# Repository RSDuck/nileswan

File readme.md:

# nileswan

An attempt at creating flash cartridge for Wonderswan.

Expect exciting things here.

## Building instructions

### Requirements

- [OSS CAD Suite](https://github.com/YosysHQ/oss-cad-suite-build) (FPGA core)
  - Requires a modified version of `icepack`, see below for more information
- [Wonderful Toolchain](https://wonderful.asie.pl/wiki/doku.php?id=getting_started) (IPL1, recovery, updater)
- CMake (MCU firmware)
- NASM (IPL0)
- Nim 2.0+ (FPGA core, IPL0)
- Ninja (MCU firmware)
- Python 3.x (SPI images, updater)
  - + `crc` library
- dd, dosfstools, mtools (emulator images)

#### icepack

For the FPGA to be ready in time, the bitstream needs to be loaded at the highest speed possible. I created a [PR](https://github.com/YosysHQ/icestorm/pull/332) for icepack which adds a setting to change this. Without it is not possible to compile the FPGA bitstream.

### Compiling

1. Make sure to fetch the Git submodules: `git submodule update --init --recursive`.
2. Run `make help` to read what build options are possible.
3. Run `make` (or `make ...`) to build the requested components.

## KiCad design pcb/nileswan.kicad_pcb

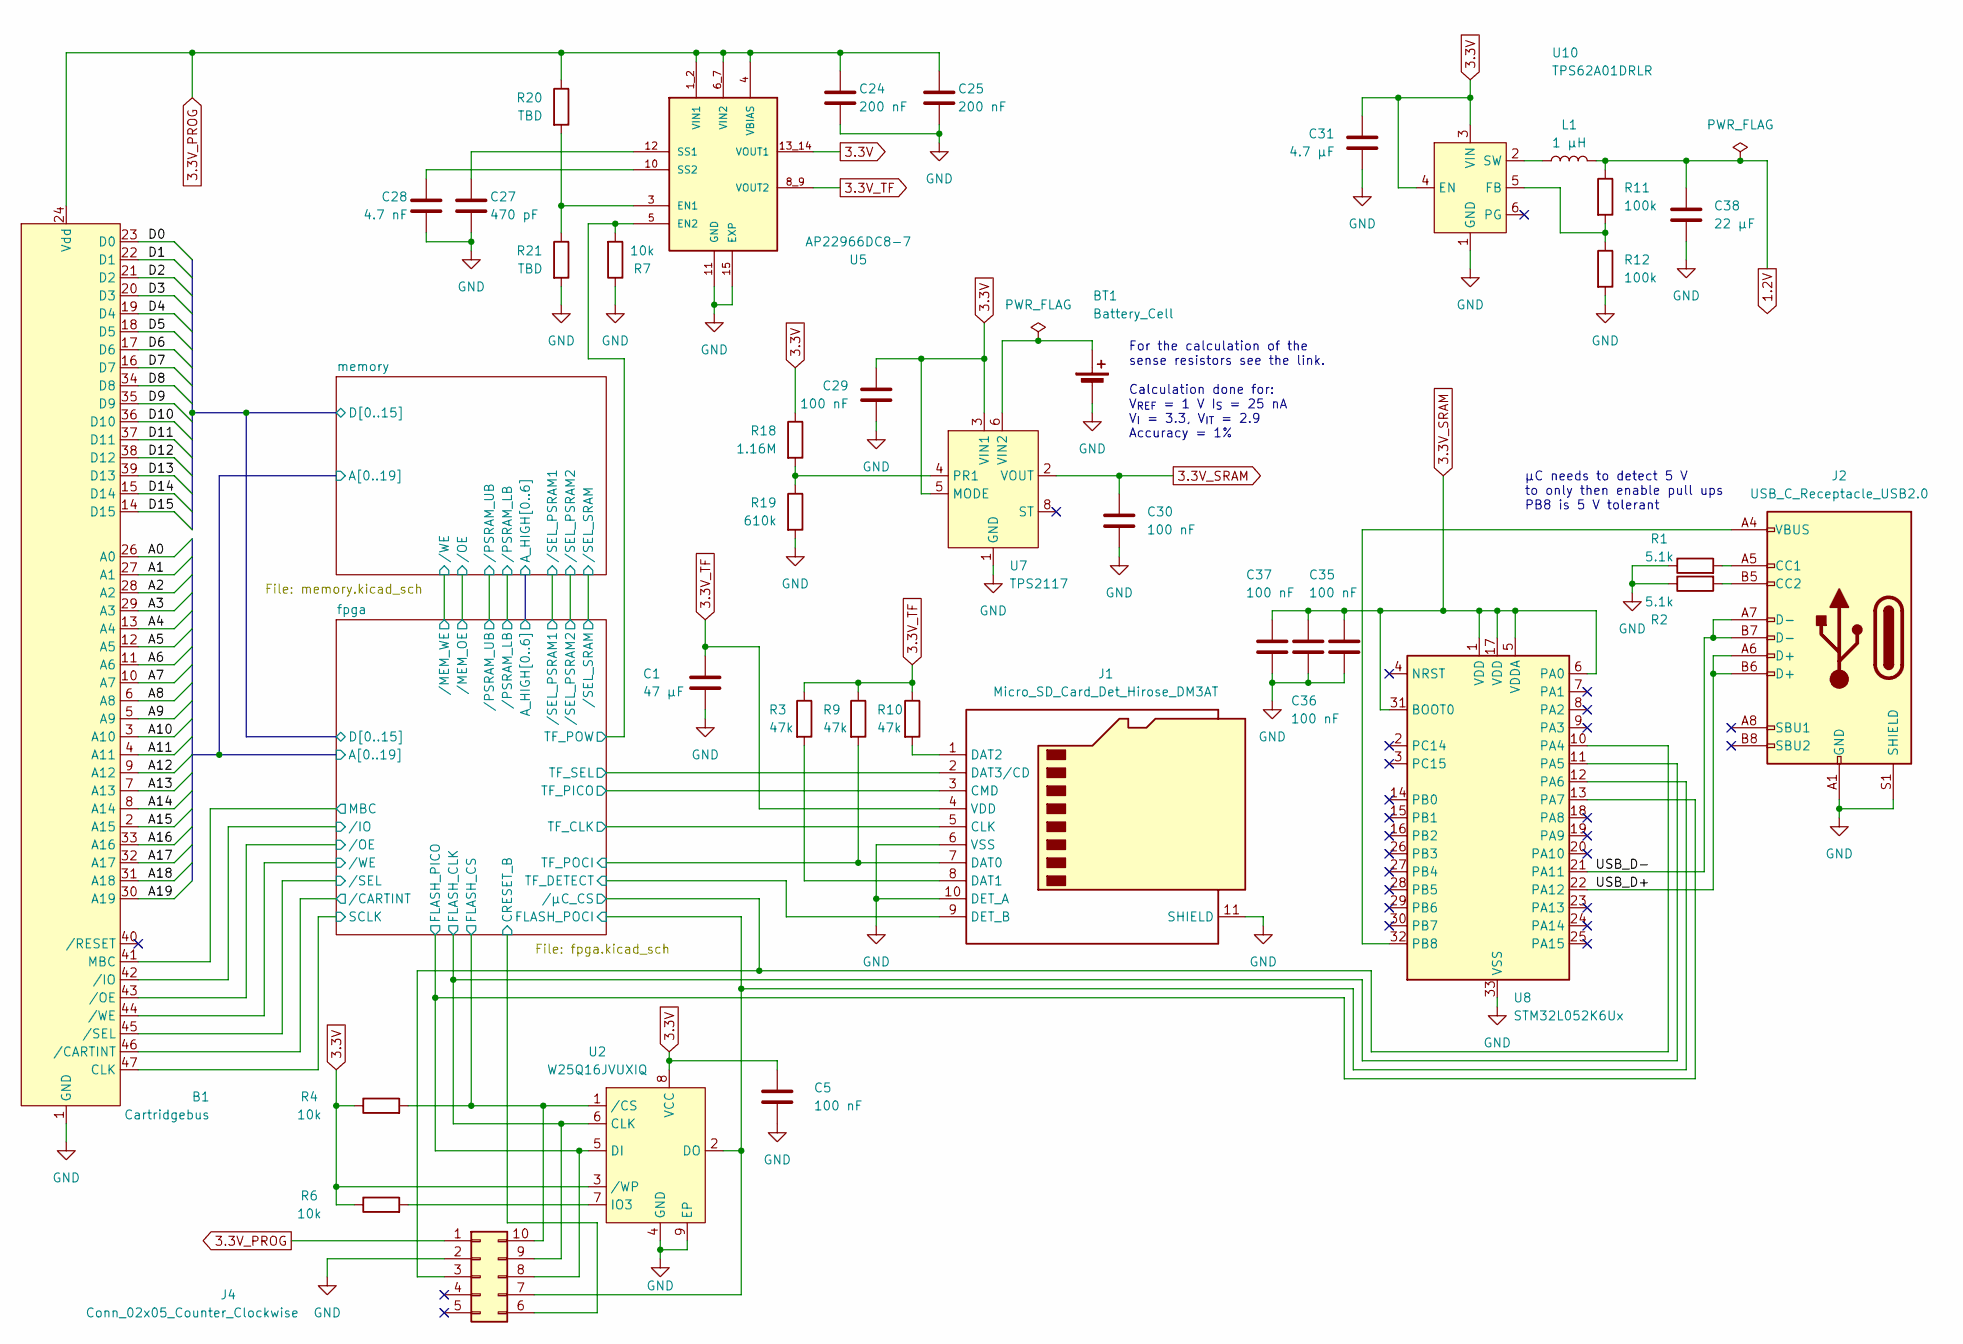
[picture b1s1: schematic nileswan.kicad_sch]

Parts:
B1: Cartridgebus; WSCartridgeBus
BT1: Battery_Cell; BAT_BAT-HLD-012-SMT
C1: 47 μF; C_0805_2012Metric
C5, C29, C30, C35, C36, C37: 100 nF; C_0402_1005Metric
C24, C25: 200 nF; C_0402_1005Metric
C27: 470 pF; C_0402_1005Metric
C28: 4.7 nF; C_0402_1005Metric
C31: 4.7 μF; C_0603_1608Metric
C38: 22 μF; C_0603_1608Metric
J1: Micro_SD_Card_Det_Hirose_DM3AT; microSD_HC_Hirose_DM3AT-SF-PEJM5
J2: USB_C_Receptacle_USB2.0; USB_C_Receptacle_GCT_USB4110
J4: Conn_02x05_Counter_Clockwise; Tag-Connect_TC2050-IDC-NL_2x05_P1.27mm_Vertical
L1: 1 μH; L_Murata_DFE201610P
R1, R2: 5.1k; R_0402_1005Metric
R3, R9, R10: 47k; R_0402_1005Metric
R4, R6, R7: 10k; R_0402_1005Metric
R11: 100k; R_0402_1005Metric
R12: 100k; C_0402_1005Metric
R18: 1.16M; R_0402_1005Metric
R19: 610k; R_0402_1005Metric
R20, R21: TBD; R_0402_1005Metric
U2: W25Q16JVUXIQ; SON50P300X200X60-9N
U5: AP22966DC8-7; IC_AP22966DC8-7; PARTREV 3-2
U7: TPS2117; SOTFL50P160X60-8N
U8: STM32L052K6Ux; QFN-32-1EP_5x5mm_P0.5mm_EP3.45x3.45mm
U10: TPS62A01DRLR; SOT-563

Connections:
1.2V: C38.1, L1.2, R11.1; also elsewhere on the board
3.3V: C5.1, C29.1, C31.1, R4.1, R6.1, R18.1, U2.3 (/WP), U2.8 (VCC), U5.13_14 (VOUT1), U7.3 (VIN1), U7.5 (MODE), U10.3 (VIN), U10.4 (EN); also elsewhere on the board
3.3V_PROG: B1.24 (Vdd), B1.25 (Vdd), C24.1, C25.1, J4.1, R20.1, U5.1_2 (VIN1), U5.4 (VBIAS), U5.6_7 (VIN2)
3.3V_SRAM: C30.1, C35.1, C36.1, C37.1, U7.2 (VOUT), U7.7 (VOUT), U8.1 (VDD), U8.5 (VDDA), U8.6 (PA0), U8.17 (VDD), U8.31 (BOOT0); also elsewhere on the board
3.3V_TF: C1.1, J1.4 (VDD), R3.1, R9.1, R10.1, U5.8_9 (VOUT2)
/USB_D+: J2.A6 (D+), J2.B6 (D+), U8.22 (PA12)
/USB_D-: J2.A7 (D-), J2.B7 (D-), U8.21 (PA11)
/fpga/A0: B1.26 (A0); also elsewhere on the board
/fpga/A1: B1.27 (A1); also elsewhere on the board
/fpga/A2: B1.28 (A2); also elsewhere on the board
/fpga/A3: B1.29 (A3); also elsewhere on the board
/fpga/A4: B1.13 (A4); also elsewhere on the board
/fpga/A5: B1.12 (A5); also elsewhere on the board
/fpga/A6: B1.11 (A6); also elsewhere on the board
/fpga/A7: B1.10 (A7); also elsewhere on the board
/fpga/A8: B1.6 (A8); also elsewhere on the board
/fpga/A9: B1.5 (A9); also elsewhere on the board
/fpga/A10: B1.3 (A10); also elsewhere on the board
/fpga/A11: B1.4 (A11); also elsewhere on the board
/fpga/A12: B1.9 (A12); also elsewhere on the board
/fpga/A13: B1.7 (A13); also elsewhere on the board
/fpga/A14: B1.8 (A14); also elsewhere on the board
/fpga/A15: B1.2 (A15); also elsewhere on the board
/fpga/A16: B1.33 (A16); also elsewhere on the board
/fpga/A17: B1.32 (A17); also elsewhere on the board
/fpga/A18: B1.31 (A18); also elsewhere on the board
/fpga/A19: B1.30 (A19); also elsewhere on the board
/fpga/CRESET_B: J4.6; also elsewhere on the board
/fpga/D0: B1.23 (D0); also elsewhere on the board
/fpga/D1: B1.22 (D1); also elsewhere on the board
/fpga/D2: B1.21 (D2); also elsewhere on the board
/fpga/D3: B1.20 (D3); also elsewhere on the board
/fpga/D4: B1.19 (D4); also elsewhere on the board
/fpga/D5: B1.18 (D5); also elsewhere on the board
/fpga/D6: B1.17 (D6); also elsewhere on the board
/fpga/D7: B1.16 (D7); also elsewhere on the board
/fpga/D8: B1.34 (D8); also elsewhere on the board
/fpga/D9: B1.35 (D9); also elsewhere on the board
/fpga/D10: B1.36 (D10); also elsewhere on the board
/fpga/D11: B1.37 (D11); also elsewhere on the board
/fpga/D12: B1.38 (D12); also elsewhere on the board
/fpga/D13: B1.39 (D13); also elsewhere on the board
/fpga/D14: B1.15 (D14); also elsewhere on the board
/fpga/D15: B1.14 (D15); also elsewhere on the board
/fpga/FLASH_CLK: J4.9, U2.6 (CLK), U8.11 (PA5); also elsewhere on the board
/fpga/FLASH_CS: J4.10, R4.2, U2.1 (/CS); also elsewhere on the board
/fpga/FLASH_PICO: J4.8, U2.5 (DI), U8.13 (PA7); also elsewhere on the board
/fpga/FLASH_POCI: J4.7, U2.2 (DO), U8.12 (PA6); also elsewhere on the board
/fpga/MBC: B1.41 (MBC); also elsewhere on the board
/fpga/SCLK: B1.47 (CLK); also elsewhere on the board
/fpga/TF_CLK: J1.5 (CLK); also elsewhere on the board
/fpga/TF_DETECT: J1.9 (DET_B); also elsewhere on the board
/fpga/TF_PICO: J1.3 (CMD); also elsewhere on the board
/fpga/TF_POCI: J1.7 (DAT0), R9.2; also elsewhere on the board
/fpga/TF_POW: R7.2, U5.5 (EN2); also elsewhere on the board
/fpga/TF_SEL: J1.2 (DAT3/CD); also elsewhere on the board
/fpga//CARTINT: B1.46 (/CARTINT); also elsewhere on the board
/fpga//IO: B1.42 (/IO); also elsewhere on the board
/fpga//OE: B1.43 (/OE); also elsewhere on the board
/fpga//SEL: B1.45 (/SEL); also elsewhere on the board
/fpga//WE: B1.44 (/WE); also elsewhere on the board
/fpga//μC_CS: J4.3, U8.10 (PA4); also elsewhere on the board
GND: B1.1 (GND), B1.48 (GND), BT1.2 (-), C1.2, C5.2, C24.2, C25.2, C27.2, C28.2, C29.2, C30.2, C31.2, C35.2, C36.2, C37.2, C38.2, J1.6 (VSS), J1.10 (DET_A), J1.11 (SHIELD), J2.A1 (GND), J2.A12 (GND), J2.B1 (GND), J2.B12 (GND), J2.S1 (SHIELD), J4.2, R1.1, R2.1, R7.1, R12.2, R19.2, R21.2, U2.4 (GND), U2.9 (EP), U5.11 (GND), U5.15 (EXP), U7.1 (GND), U8.33 (VSS), U10.1 (GND); also elsewhere on the board
unnamed: BT1.1 (+), U7.6 (VIN2)
unnamed: J1.8 (DAT1), R3.2
unnamed: J1.1 (DAT2), R10.2
unnamed: J2.A5 (CC1), R1.2
unnamed: J2.B5 (CC2), R2.2
unnamed: R6.2, U2.7 (IO3)
unnamed: R20.2, R21.1, U5.3 (EN1)
unnamed: C27.1, U5.12 (SS1)
unnamed: C28.1, U5.10 (SS2)
unnamed: R18.2, R19.1, U7.4 (PR1)
unnamed: J2.A4 (VBUS), J2.A9 (VBUS), J2.B4 (VBUS), J2.B9 (VBUS), U8.32 (PB8)
unnamed: R11.2, R12.1, U10.5 (FB)
unnamed: L1.1, U10.2 (SW)

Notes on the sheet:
μC needs to detect 5 V to only then enable pull ups PB8 is 5 V tolerant
For the calculation of the sense resistors see the link. Calculation done for: V_{REF} = 1 V I_{S} = 25 nA V_{I} = 3.3, V_{IT} = 2.9 Accuracy = 1%

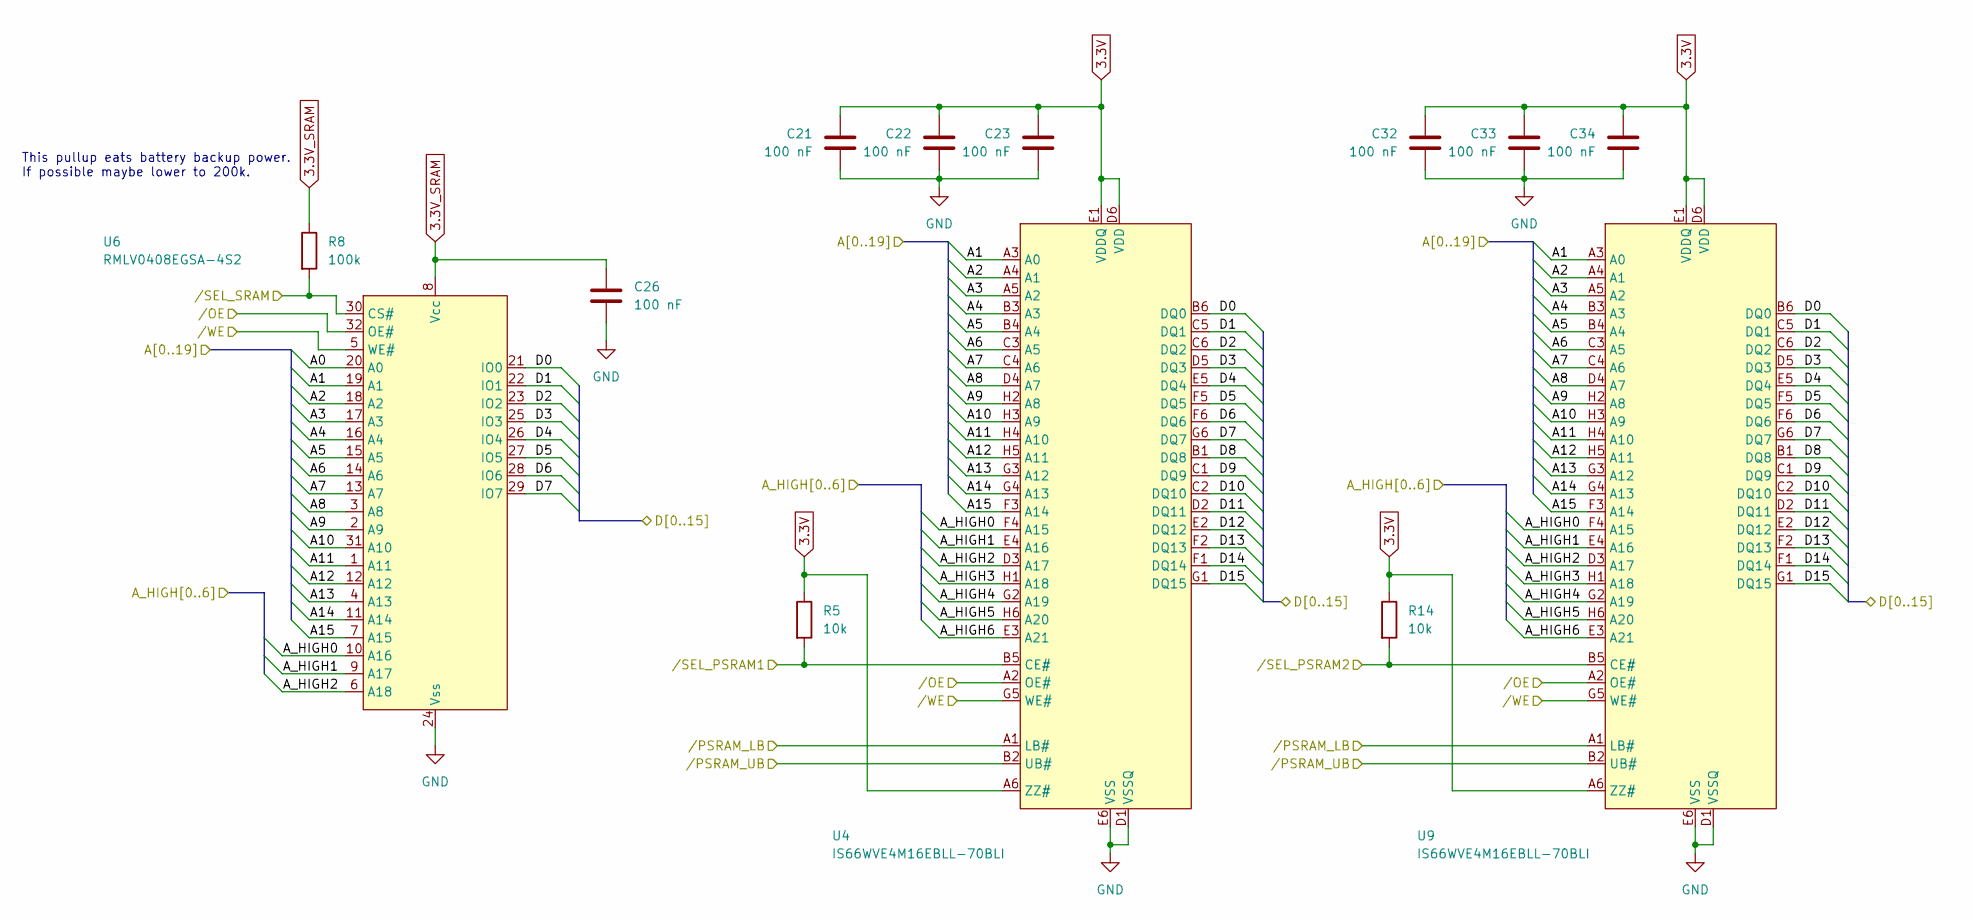
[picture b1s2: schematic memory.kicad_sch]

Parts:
C21, C22, C23, C26, C32, C33, C34: 100 nF; C_0402_1005Metric
R5, R14: 10k; R_0402_1005Metric
R8: 100k; R_0402_1005Metric
U4, U9: IS66WVE4M16EBLL-70BLI; BGA-48_6x8_6.0x8.0mm
U6: RMLV0408EGSA-4S2; sTSOP-32

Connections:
3.3V: C21.2, C22.2, C23.2, C32.2, C33.2, C34.2, R5.1, R14.1, U4.A6 (ZZ#), U4.D6 (VDD), U4.E1 (VDDQ), U9.A6 (ZZ#), U9.D6 (VDD), U9.E1 (VDDQ); also elsewhere on the board
3.3V_SRAM: C26.2, R8.1, U6.8 (Vcc); also elsewhere on the board
/fpga/A0: U6.20 (A0); also elsewhere on the board
/fpga/A1: U4.A3 (A0), U6.19 (A1), U9.A3 (A0); also elsewhere on the board
/fpga/A2: U4.A4 (A1), U6.18 (A2), U9.A4 (A1); also elsewhere on the board
/fpga/A3: U4.A5 (A2), U6.17 (A3), U9.A5 (A2); also elsewhere on the board
/fpga/A4: U4.B3 (A3), U6.16 (A4), U9.B3 (A3); also elsewhere on the board
/fpga/A5: U4.B4 (A4), U6.15 (A5), U9.B4 (A4); also elsewhere on the board
/fpga/A6: U4.C3 (A5), U6.14 (A6), U9.C3 (A5); also elsewhere on the board
/fpga/A7: U4.C4 (A6), U6.13 (A7), U9.C4 (A6); also elsewhere on the board
/fpga/A8: U4.D4 (A7), U6.3 (A8), U9.D4 (A7); also elsewhere on the board
/fpga/A9: U4.H2 (A8), U6.2 (A9), U9.H2 (A8); also elsewhere on the board
/fpga/A10: U4.H3 (A9), U6.31 (A10), U9.H3 (A9); also elsewhere on the board
/fpga/A11: U4.H4 (A10), U6.1 (A11), U9.H4 (A10); also elsewhere on the board
/fpga/A12: U4.H5 (A11), U6.12 (A12), U9.H5 (A11); also elsewhere on the board
/fpga/A13: U4.G3 (A12), U6.4 (A13), U9.G3 (A12); also elsewhere on the board
/fpga/A14: U4.G4 (A13), U6.11 (A14), U9.G4 (A13); also elsewhere on the board
/fpga/A15: U4.F3 (A14), U6.7 (A15), U9.F3 (A14); also elsewhere on the board
/fpga/A_HIGH0: U4.F4 (A15), U6.10 (A16), U9.F4 (A15); also elsewhere on the board
/fpga/A_HIGH1: U4.E4 (A16), U6.9 (A17), U9.E4 (A16); also elsewhere on the board
/fpga/A_HIGH2: U4.D3 (A17), U6.6 (A18), U9.D3 (A17); also elsewhere on the board
/fpga/A_HIGH3: U4.H1 (A18), U9.H1 (A18); also elsewhere on the board
/fpga/A_HIGH4: U4.G2 (A19), U9.G2 (A19); also elsewhere on the board
/fpga/A_HIGH5: U4.H6 (A20), U9.H6 (A20); also elsewhere on the board
/fpga/A_HIGH6: U4.E3 (A21), U9.E3 (A21); also elsewhere on the board
/fpga/D0: U4.B6 (DQ0), U6.21 (IO0), U9.B6 (DQ0); also elsewhere on the board
/fpga/D1: U4.C5 (DQ1), U6.22 (IO1), U9.C5 (DQ1); also elsewhere on the board
/fpga/D2: U4.C6 (DQ2), U6.23 (IO2), U9.C6 (DQ2); also elsewhere on the board
/fpga/D3: U4.D5 (DQ3), U6.25 (IO3), U9.D5 (DQ3); also elsewhere on the board
/fpga/D4: U4.E5 (DQ4), U6.26 (IO4), U9.E5 (DQ4); also elsewhere on the board
/fpga/D5: U4.F5 (DQ5), U6.27 (IO5), U9.F5 (DQ5); also elsewhere on the board
/fpga/D6: U4.F6 (DQ6), U6.28 (IO6), U9.F6 (DQ6); also elsewhere on the board
/fpga/D7: U4.G6 (DQ7), U6.29 (IO7), U9.G6 (DQ7); also elsewhere on the board
/fpga/D8: U4.B1 (DQ8), U9.B1 (DQ8); also elsewhere on the board
/fpga/D9: U4.C1 (DQ9), U9.C1 (DQ9); also elsewhere on the board
/fpga/D10: U4.C2 (DQ10), U9.C2 (DQ10); also elsewhere on the board
/fpga/D11: U4.D2 (DQ11), U9.D2 (DQ11); also elsewhere on the board
/fpga/D12: U4.E2 (DQ12), U9.E2 (DQ12); also elsewhere on the board
/fpga/D13: U4.F2 (DQ13), U9.F2 (DQ13); also elsewhere on the board
/fpga/D14: U4.F1 (DQ14), U9.F1 (DQ14); also elsewhere on the board
/fpga/D15: U4.G1 (DQ15), U9.G1 (DQ15); also elsewhere on the board
/fpga//MEM_OE: U4.A2 (OE#), U6.32 (OE#), U9.A2 (OE#); also elsewhere on the board
/fpga//MEM_WE: U4.G5 (WE#), U6.5 (WE#), U9.G5 (WE#); also elsewhere on the board
/fpga//PSRAM_LB: U4.A1 (LB#), U9.A1 (LB#); also elsewhere on the board
/fpga//PSRAM_UB: U4.B2 (UB#), U9.B2 (UB#); also elsewhere on the board
/fpga//SEL_PSRAM1: R5.2, U4.B5 (CE#); also elsewhere on the board
/fpga//SEL_PSRAM2: R14.2, U9.B5 (CE#); also elsewhere on the board
/fpga//SEL_SRAM: R8.2, U6.30 (CS#); also elsewhere on the board
GND: C21.1, C22.1, C23.1, C26.1, C32.1, C33.1, C34.1, U4.D1 (VSSQ), U4.E6 (VSS), U6.24 (Vss), U9.D1 (VSSQ), U9.E6 (VSS); also elsewhere on the board

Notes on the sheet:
This pullup eats battery backup power. If possible maybe lower to 200k.

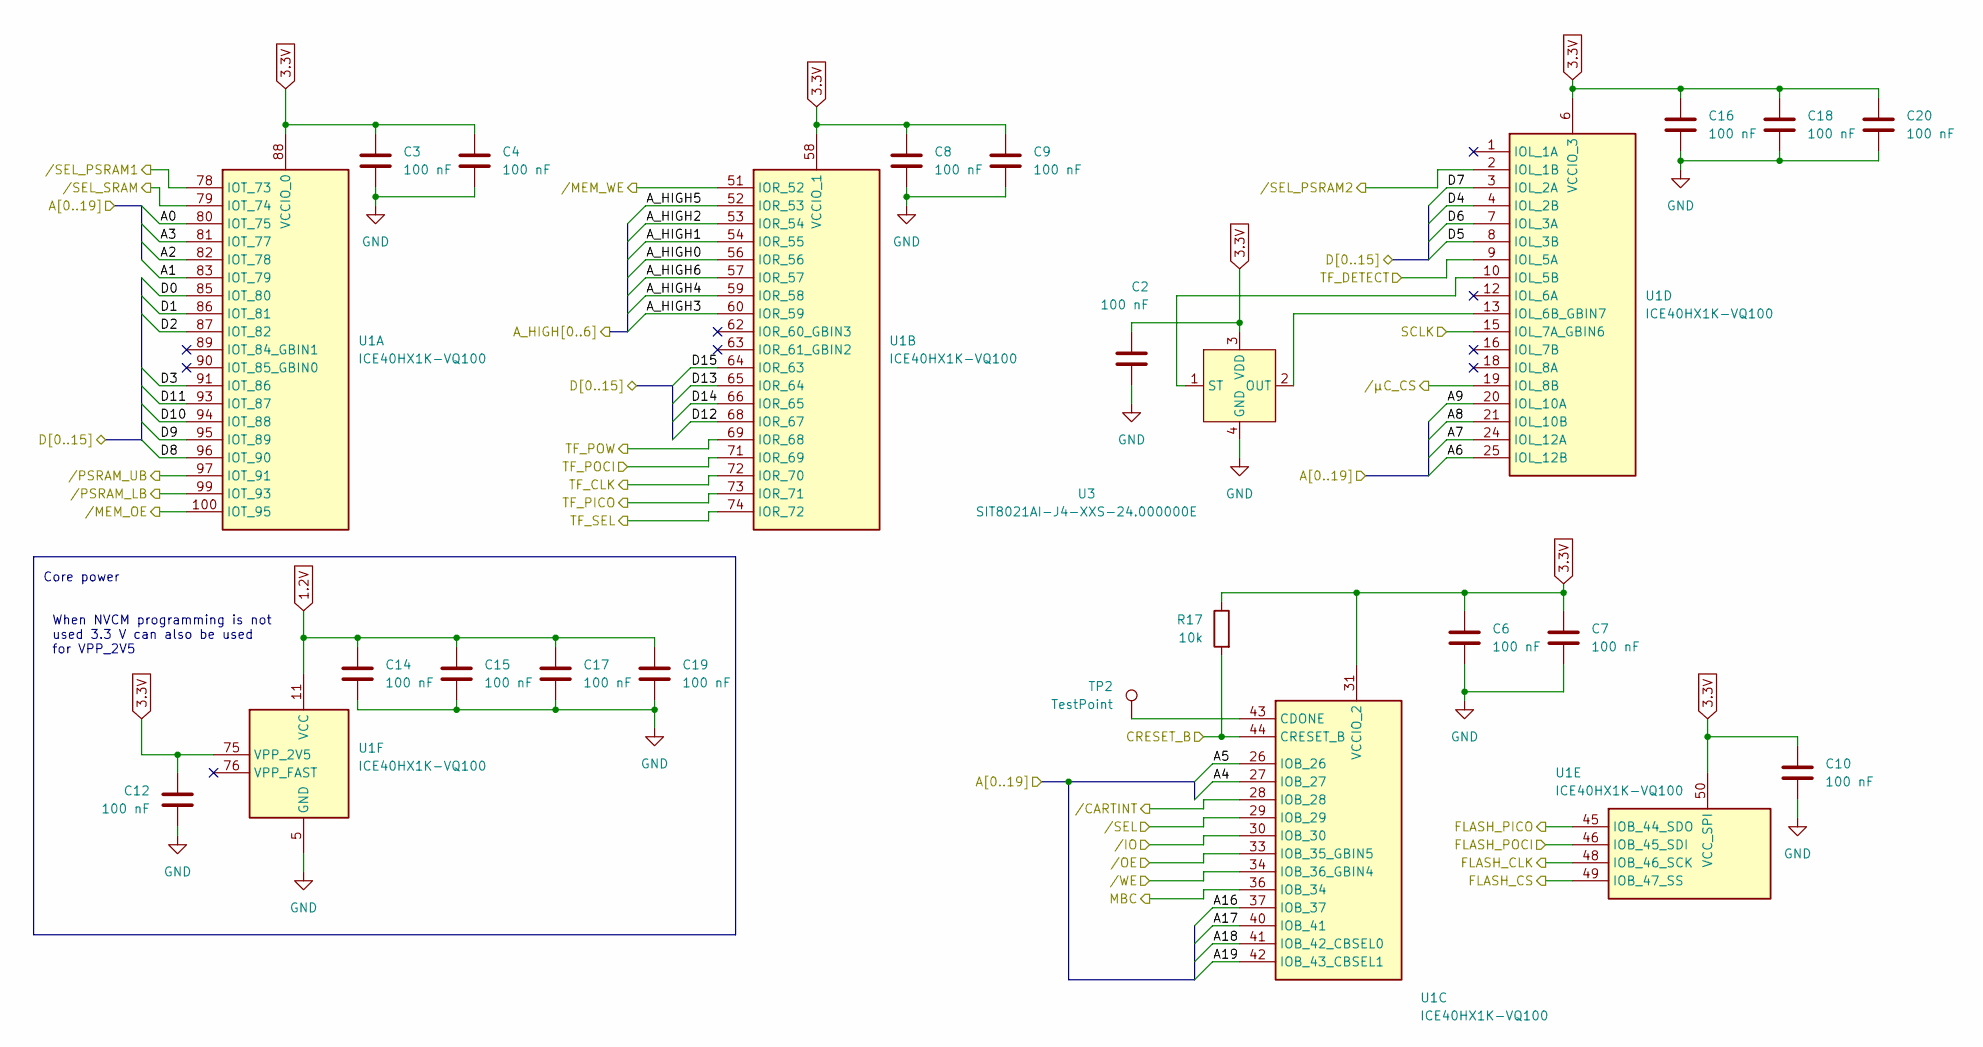
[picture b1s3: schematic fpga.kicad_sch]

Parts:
C2, C3, C4, C6, C7, C8, C9, C10, C12, C14, C15, C16, C17, C18, C19, C20: 100 nF; C_0402_1005Metric
R17: 10k; R_0402_1005Metric
TP2: TestPoint; TestPoint_Pad_D1.0mm
U1: ICE40HX1K-VQ100; VQFP-100_14x14mm_P0.5mm
U3: SIT8021AI-J4-XXS-24.000000E; BGA4N41X100P2X2_84X154X60N

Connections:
1.2V: C14.1, C15.1, C17.1, C19.1, U1.11 (VCC), U1.35 (VCC), U1.61 (VCC), U1.77 (VCC); also elsewhere on the board
3.3V: C2.1, C3.1, C4.1, C6.1, C7.1, C8.1, C9.1, C10.1, C12.1, C16.1, C18.1, C20.1, R17.1, U1.6 (VCCIO_3), U1.14 (VCCIO_3), U1.22 (VCCIO_3), U1.31 (VCCIO_2), U1.38 (VCCIO_2), U1.50 (VCC_SPI), U1.58 (VCCIO_1), U1.67 (VCCIO_1), U1.75 (VPP_2V5), U1.88 (VCCIO_0), U1.92 (VCCIO_0), U3.3 (VDD); also elsewhere on the board
/fpga/A0: U1.80 (IOT_75); also elsewhere on the board
/fpga/A1: U1.83 (IOT_79); also elsewhere on the board
/fpga/A2: U1.82 (IOT_78); also elsewhere on the board
/fpga/A3: U1.81 (IOT_77); also elsewhere on the board
/fpga/A4: U1.27 (IOB_27); also elsewhere on the board
/fpga/A5: U1.26 (IOB_26); also elsewhere on the board
/fpga/A6: U1.25 (IOL_12B); also elsewhere on the board
/fpga/A7: U1.24 (IOL_12A); also elsewhere on the board
/fpga/A8: U1.21 (IOL_10B); also elsewhere on the board
/fpga/A9: U1.20 (IOL_10A); also elsewhere on the board
/fpga/A16: U1.37 (IOB_37); also elsewhere on the board
/fpga/A17: U1.40 (IOB_41); also elsewhere on the board
/fpga/A18: U1.41 (IOB_42_CBSEL0); also elsewhere on the board
/fpga/A19: U1.42 (IOB_43_CBSEL1); also elsewhere on the board
/fpga/A_HIGH0: U1.56 (IOR_56); also elsewhere on the board
/fpga/A_HIGH1: U1.54 (IOR_55); also elsewhere on the board
/fpga/A_HIGH2: U1.53 (IOR_54); also elsewhere on the board
/fpga/A_HIGH3: U1.60 (IOR_59); also elsewhere on the board
/fpga/A_HIGH4: U1.59 (IOR_58); also elsewhere on the board
/fpga/A_HIGH5: U1.52 (IOR_53); also elsewhere on the board
/fpga/A_HIGH6: U1.57 (IOR_57); also elsewhere on the board
/fpga/CRESET_B: R17.2, U1.44 (CRESET_B); also elsewhere on the board
/fpga/D0: U1.85 (IOT_80); also elsewhere on the board
/fpga/D1: U1.86 (IOT_81); also elsewhere on the board
/fpga/D2: U1.87 (IOT_82); also elsewhere on the board
/fpga/D3: U1.91 (IOT_86); also elsewhere on the board
/fpga/D4: U1.4 (IOL_2B); also elsewhere on the board
/fpga/D5: U1.8 (IOL_3B); also elsewhere on the board
/fpga/D6: U1.7 (IOL_3A); also elsewhere on the board
/fpga/D7: U1.3 (IOL_2A); also elsewhere on the board
/fpga/D8: U1.96 (IOT_90); also elsewhere on the board
/fpga/D9: U1.95 (IOT_89); also elsewhere on the board
/fpga/D10: U1.94 (IOT_88); also elsewhere on the board
/fpga/D11: U1.93 (IOT_87); also elsewhere on the board
/fpga/D12: U1.68 (IOR_67); also elsewhere on the board
/fpga/D13: U1.65 (IOR_64); also elsewhere on the board
/fpga/D14: U1.66 (IOR_65); also elsewhere on the board
/fpga/D15: U1.64 (IOR_63); also elsewhere on the board
/fpga/FLASH_CLK: U1.48 (IOB_46_SCK); also elsewhere on the board
/fpga/FLASH_CS: U1.49 (IOB_47_SS); also elsewhere on the board
/fpga/FLASH_PICO: U1.45 (IOB_44_SDO); also elsewhere on the board
/fpga/FLASH_POCI: U1.46 (IOB_45_SDI); also elsewhere on the board
/fpga/MBC: U1.36 (IOB_34); also elsewhere on the board
/fpga/SCLK: U1.15 (IOL_7A_GBIN6); also elsewhere on the board
/fpga/TF_CLK: U1.72 (IOR_70); also elsewhere on the board
/fpga/TF_DETECT: U1.9 (IOL_5A); also elsewhere on the board
/fpga/TF_PICO: U1.73 (IOR_71); also elsewhere on the board
/fpga/TF_POCI: U1.71 (IOR_69); also elsewhere on the board
/fpga/TF_POW: U1.69 (IOR_68); also elsewhere on the board
/fpga/TF_SEL: U1.74 (IOR_72); also elsewhere on the board
/fpga//CARTINT: U1.28 (IOB_28); also elsewhere on the board
/fpga//IO: U1.30 (IOB_30); also elsewhere on the board
/fpga//MEM_OE: U1.100 (IOT_95); also elsewhere on the board
/fpga//MEM_WE: U1.51 (IOR_52); also elsewhere on the board
/fpga//OE: U1.33 (IOB_35_GBIN5); also elsewhere on the board
/fpga//PSRAM_LB: U1.99 (IOT_93); also elsewhere on the board
/fpga//PSRAM_UB: U1.97 (IOT_91); also elsewhere on the board
/fpga//SEL: U1.29 (IOB_29); also elsewhere on the board
/fpga//SEL_PSRAM1: U1.78 (IOT_73); also elsewhere on the board
/fpga//SEL_PSRAM2: U1.2 (IOL_1B); also elsewhere on the board
/fpga//SEL_SRAM: U1.79 (IOT_74); also elsewhere on the board
/fpga//WE: U1.34 (IOB_36_GBIN4); also elsewhere on the board
/fpga//μC_CS: U1.19 (IOL_8B); also elsewhere on the board
GND: C2.2, C3.2, C4.2, C6.2, C7.2, C8.2, C9.2, C10.2, C12.2, C14.2, C15.2, C16.2, C17.2, C18.2, C19.2, C20.2, U1.5 (GND), U1.17 (GND), U1.23 (GND), U1.32 (GND), U1.39 (GND), U1.47 (GND), U1.55 (GND), U1.70 (GND), U1.84 (GND), U1.98 (GND), U3.4 (GND); also elsewhere on the board
unnamed: TP2.1, U1.43 (CDONE)
unnamed: U1.10 (IOL_5B), U3.1 (ST)
unnamed: U1.13 (IOL_6B_GBIN7), U3.2 (OUT)

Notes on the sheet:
Core power
When NVCM programming is not used 3.3 V can also be used for VPP_2V5

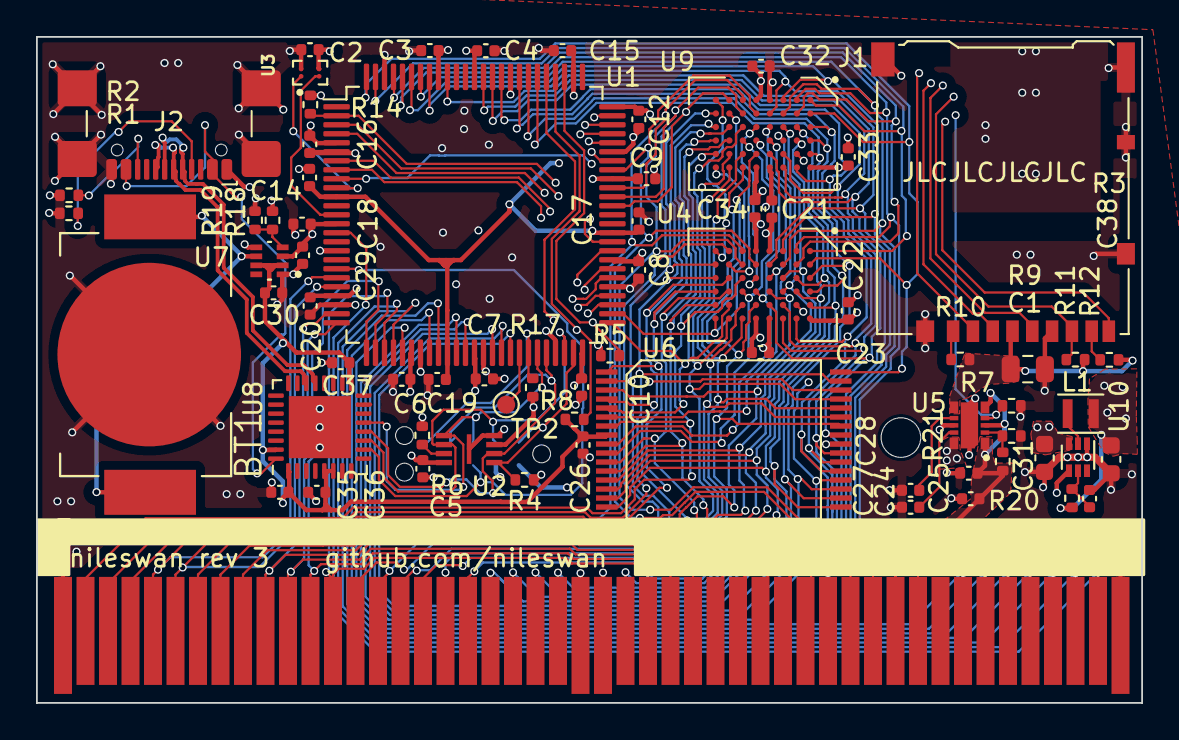
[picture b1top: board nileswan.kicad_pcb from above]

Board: 4 copper layers, 61.4 x 37.0 mm, 71 parts (1 on the bottom side), 93 nets.

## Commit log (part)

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2023-08-05 remove stray dot
2023-08-05 markdown fixes
2023-08-23 add license
2023-08-23 add mechanical details section
2023-08-23 first prototype of the PCB
2023-09-28 relicense to strongly reciprocal CERN OSHW 2
2023-09-28 minor additions to docs
2023-09-28 relicense again, this time to GPLv3 I should have done this from the start. It's not optimal for hardware and "gateware", but it's much easier to deal with in terms of compability with other licenses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
2023-12-05 document write data behaviour
2023-12-27 initial progress on firmware/fpga side
2023-12-28 improve makefile, gitignore, fix build
2024-01-06 use dedicated asm file for register definitions
2024-01-13 improve fpga makefile
2024-01-14 add documentation on self flashing
2024-01-14 load and start IPL1 into PSRAM
2024-01-29 preliminary prog env
2024-01-29 clarify RX/TX buffer double buffering
2024-01-29 clarify SPI transfer length
2024-02-01 address feedback from asie and some other additions
2024-02-04 prevent Github from saying this is all html
2024-02-07 second pcb iteration
2024-02-07 fpga/ipl0, ipl1: new implementation
    Rewritten from scratch.
    - Compliant with the current (as of writing) programming environment
    specification.
    - IPL1 now supports running a simple self-test (hold X3+A on boot).
    - IPL1 now loads a "menu.ws" file from the root of the SD card.
2024-02-07 fpga/ipl0, ipl1: move ipl1 to 0x60, add code to preserve initial register state, add keybind to load alt ipl1
2024-02-08 ipl1: add fancy loading screen
2024-02-08 ipl1: add SPI timeout handling
2024-02-08 ipl1: rewrite nile_spi_wait_busy to ASM, set ~0.9s timeout
2024-02-08 ipl1: minor optimizations
2024-02-09 ipl1: card driver, logging improvements
2024-02-10 ipl1: deinitialize hardware on failure to save power
2024-02-10 first bit errata for new pcb iteration
2024-02-10 document icepack speed quirk
2024-02-10 adapt gateware to pcb changes, new SPI interface and refactoring
2024-02-11 ipl1: fix multi transfer handling
2024-02-11 ipl1: rewrite nile_spi_tx in ASM
2024-02-11 ipl1: power off card on initialization failure, cleanup init code
2024-02-11 ipl1: clock in more 0xFF bytes, use near memset
2024-02-12 update status
2024-02-14 ipl1: all the fixes required to boot on hardware
2024-02-14 ipl1: split boot and selftest
2024-02-14 ipl0: support loading selftest from alternate address
2024-02-14 ipl1: selftest: basic menu framework, quick test/io speed control options
2024-02-14 ipl1: selftest: add SRAM read persistence test
2024-02-14 ipl1: disable SRAM/cart IO waitstates on Color
2024-02-14 improve SPI bench
2024-02-14 ipl1: restore "program" rule
2024-02-14 ipl1: restore "program" rule properly
2024-02-15 ipl1: load /nileswan/menu.ws as opposed to /menu.ws
2024-02-18 ipl0: store WS/PCv2 console type
2024-03-09 add flashing of the self test binary
2024-03-17 remove old PSRAM tester
2024-04-02 pcb revision 3 and 16 MB PSRAM support
2024-04-02 better wording
2024-04-05 some optimisations to save logic elements from 415 down to 373 also implement PCv2 boot (untested)
2024-04-27 Label 16 MB PSRAM quick test as such
2024-04-27 WIP shell
2024-04-27 use correct footprint for R12
2024-04-27 remove line I forgot to remove in progenv
2024-05-01 implement new combined SPI cs/device select also make signal naming a bit more consistent
2024-05-01 add missing constant change
2024-05-04 set right commit for opencm3
2024-05-04 move simulated SPI device into a macro
2024-05-04 document another PCB mistake
2024-05-29 update regarding icepack oscillator speed
2024-05-29 improve test benches
2024-06-07 MCU firmware flashing and basic SPI communication
2024-07-17 erase 32kb blocks for IPL1 ensures that no leftover data might be loaded
2024-08-05 implement mcu reset in POW_CNT
2024-08-05 implement per address space mapping enable bits for bank masking
2024-08-05 implement ipc buffer
2024-08-06 commit missing code in bootrom module
2024-08-06 ipl1: use libnile instead of local fork (wip)
2024-08-06 ipl1: add libnile submodule, restore diskio_detail_code
2024-08-06 add ipl1 to Makefile, update libnile
2024-08-06 ipl1: comment out flash/MCU selftest code for now
2024-08-07 ipl0, ipl1: add ipl1 header, move to only two ipl1 images, change area for storing IPL0->IPL1 data
2024-08-07 ipl1: move from LZSA2 to ZX0, saving ~128 bytes
2024-08-07 libnile: update
2024-08-07 updater: commit
2024-08-09 ipl0, ipl1: restore MCU comm test to selftest
2024-08-09 ipl0: fix spiStartRead bug
2024-08-09 ipl1/selftest: visual fixes for MCU comm test
2024-08-10 ipl1: fixes
2024-08-11 ipl0, ipl1: move to libnile over bundled code, fixes/tweaks, add updater tool
2024-08-11 allow setting icepack version via a environment variable
2024-08-11 correct addresses for external ipl1 flashing
2024-08-11 ipl1: push MCU SPI serial port testing code
2024-08-11 ipl1: selftest MCU fixes
2024-11-24 FPGA side mcu boot0 workaround for pcb rev4 where boot0 is connected to POCI instead of PICO
2024-11-26 firmware: push new LL/tinyusb-based version
2024-11-26 firmware: build fixes
2024-12-11 ipl0, ipl1, updater: clean up
2024-12-11 ipl0: calculate correct checksum for header
2024-12-12 updater: add building .bin and .ws files
2024-12-12 updater: fix typo
2024-12-15 firmware: code drop
2024-12-16 ipl1, libnile: fix IPC initialization
2024-12-16 firmware: add ID command
2024-12-17 firmware: fix race condition on startup
2024-12-17 firmware: add second CDC port for MCU firmware debug
2024-12-18 firmware: stability improvements
2024-12-30 EEPROM emulation FPGA side also allow disabling mapper registers and also making SRAM disableable
2024-12-30 move EEPROM into a new register
2024-12-30 move EMU_CNT one address farther that one was already used
2024-12-30 have separate bit for disabling SRAM
2024-12-30 libnile, updater: update for new progenv
2024-12-31 make enable sram bit readable in POW_CNT
2025-01-01 ipl1: initialize IPC also in safe mode
2025-01-01 docs, manifest, ipl0: adjust SPI flash layout
2025-01-01 manifest, ipl1, recovery: add recovery binary
2025-01-01 ipl1/safe: verify loaded recovery program
2025-01-02 EEPROM SPI output and RTC
2025-01-02 RTC cleanup
2025-01-05 firmware: fixes, improvements
2025-01-06 updater: support non-multiple-of-256 FLASH files in manifest_to_rom
2025-01-06 Makefile: add rules for building an emulator bundle, firmware
2025-01-06 chore: document dist-emu requirements
2025-01-06 make anti output glitch part actually work
2025-01-06 lift external selects when /OE and /WE are high otherwise PSRAM maximum access time might be overrun and memory is not refreshed
2025-01-06 firmware: start working on STM32U0 build
2025-02-20 add option for initial U0 option byte setup in safe IPL1
2025-02-20 update libnile
2025-02-21 implement SPI transfer stopping
2025-03-11 remove X state, yosys doesn't seem to like it
2025-03-11 SPI transaction stop test
2025-03-11 U0 mcu firmware code fixes
2025-03-11 fix U0 USB hot plugging for good
2025-03-12 make μC busy/BOOT0 line open drain
2025-03-12 U0 is now the default MCU target
2025-03-13 ipl1, recovery: keep BIOS unlocked for recovery mode
2025-03-14 firmware: minor U0 optimizations
2025-03-16 nit: fix RTC command enum order
2025-03-16 ipl1: smooth progress bar
2025-03-16 ipl1: disk/drive -> storage
2025-03-16 ipl1: minor size savings in fatfs
2025-03-20 firmware: add sleep support (todo: reclocking)
2025-03-22 recovery: initial console implementation
2025-03-22 recovery: fix newlines
2025-03-22 recovery: simple text wrapping
2025-03-22 ipl1: revert minor size savings
2025-03-22 ipl1: add way to boot IPL1 from BootFriend in case of an IPL1 brick
2025-03-22 recovery: add ID logging
2025-03-22 recovery: add rudimentary storage card test
2025-03-23 firmware: add simple header format
2025-03-23 chore: fix firmware not rebuilding itself
2025-03-23 firmware: switch from HSI16 to MSI
2025-03-27 recovery: add font data
2025-03-29 firmware: fix MSI clock, add USB shutoff, reclocking
2025-03-29 firmware: fix MCU_PIN_BAT detection
2025-03-29 firmware: READY -> BUSY
2025-03-29 firmware: spi: deinit/init improvements
2025-03-29 updater: fix poweroff
2025-03-29 fix RTC FPGA - the enum seems to not work with yosys - fix length of undefined commands - unset busy bit together with ready bit
2025-03-29 remove X bit from FPGA mapper too
2025-03-29 firmware, recovery: minor touchups
2025-03-30 firmware: fix MCU_PIN_FPGA_BUSY
2025-03-30 fix transfering received data to RTC data register
2025-03-30 check for /IO and /Sel for all IO register writes
2025-03-30 actually RTC read transfer to register was the right way around
2025-03-30 rtc, spi: fix rtc reset, minor cleanup
2025-03-30 firmware: spi: use DMA for 0xFF response padding in native mode
2025-03-30 implement EEPROM ack
2025-03-30 firmware: mcu, spi: busy bit tweaks, voltage regulation
2025-03-30 implement RTC ack
2025-03-30 pass falling edge signal of mcu ready into RTC module
2025-03-30 firmware: tweaks
2025-03-31 updater: allow <1MB images, stability improvements
2025-04-01 recovery, updater: rework directory layout to allow for shared code
2025-04-01 updater: use recovery user interface
2025-04-01 implement second ack for RTC transfers
2025-04-02 flash memory flashing emulation (untested)
2025-04-02 add flash FSM test
2025-04-02 ipl1: additional logging on crash
2025-04-04 ipl0: fix IEEPROM write unprotect
2025-04-04 docs: move to hugo-geekdoc
2025-04-04 implement boot splash bypass when button is pressed
2025-04-04 docs, ipl0: add factory IPL1 recovery procedure
2025-04-04 add FPGA side of FPGA warmbooting
2025-04-04 RTC WIP
2025-04-04 ip1l, manifest: split boot and factory IPL1, add warmboot
2025-04-05 fpga: enable lockout ports
2025-04-05 ipl1: fix IPC restore on warmboot
2025-04-05 recovery: fix flash FSM test
2025-04-05 updater: allow including >65535 byte files in manifest
2025-04-05 recovery: implement TF card benchmarks
2025-04-05 docs: update IPC card status docs
2025-04-06 make RTC work (hopefully) - redo part of the state machine - make command start clear the ready bit - (workaround?) delay ack signal by 64 cycles, then everything starts to work
2025-04-06 chore: update libnile, separate out clean operations
2025-04-06 fpga: make the flash FSM only apply to the RAM area
2025-04-06 fpga: add support for 8-bit ROM bus width
2025-04-06 fpga: code review fixes
2025-04-06 docs: document troubleshooting more extensively
2025-04-06 updater: add support for MCU flashing, store Git commit hash/file digest
2025-04-06 add RS flag handling similar to HAL
2025-04-06 remove RTC workaround of adding extra cycles until ack is used
2025-04-06 firmware: spi: fix first byte transmitted after mode switch being 0xFF
2025-04-06 fpga, libnile: change nile unlock value from 0xFD to 0xDD
2025-04-06 recovery: alternate 0x15 and 0x17 for RTC stability test
2025-04-07 firmware: use BYPSHAD for RTC readouts
2025-04-07 firmware: improve RTC write and 12-hour mode accuracy
2025-04-07 firmware: emulate AM/PM bit in 24-hour mode, more invalid value handling
2025-04-07 fix register enable_rom_8bit_bus register definition
2025-04-07 recovery: ASM-based fetch_rtc_time() for stability test
2025-04-07 firmware: 12<->24-hour time conversion on status write
2025-04-07 add /MCUInt to FPGA pin definitions
2025-04-08 firmware, fpga: initial IRQ port implementation
2025-04-08 docs: move MCU protocol to dev docs
2025-04-08 firmware: initial RTC interrupt implementation (mostly correct, somewhat inefficient)
2025-04-09 docs: update README
2025-04-09 docs: add missing links
2025-04-09 ipl0, ipl1: reset/preserve more sytsem state
2025-04-09 docs: update emulator support chart
2025-04-10 docs: adjuts base URL
2025-04-12 docs: add favicon
2025-04-12 larger SPI buffer size
2025-04-12 fpga, ipl0, libnile, docs: swap port 0xE3 and 0xE6
2025-04-12 docs: updates
2025-04-13 recovery: test writes while doing write benchmark
2025-04-13 docs, fpga: add BOARD_REVISION
2025-04-13 docs: documentation work
2025-04-13 docs: remove more redundant information
2025-04-13 recovery: more accurate read/write speed measurement
2025-04-15 firmware: avoid SRAM2 retention when unnecessary
2025-04-19 ipl1: load to bank 0xFF downwards
2025-04-20 libnile, updater: add per-board-revision updates
2025-04-21 firmware: better handling of out-of-bounds RTC writes
2025-04-21 firmware: add CDC output mode, document a few bits
